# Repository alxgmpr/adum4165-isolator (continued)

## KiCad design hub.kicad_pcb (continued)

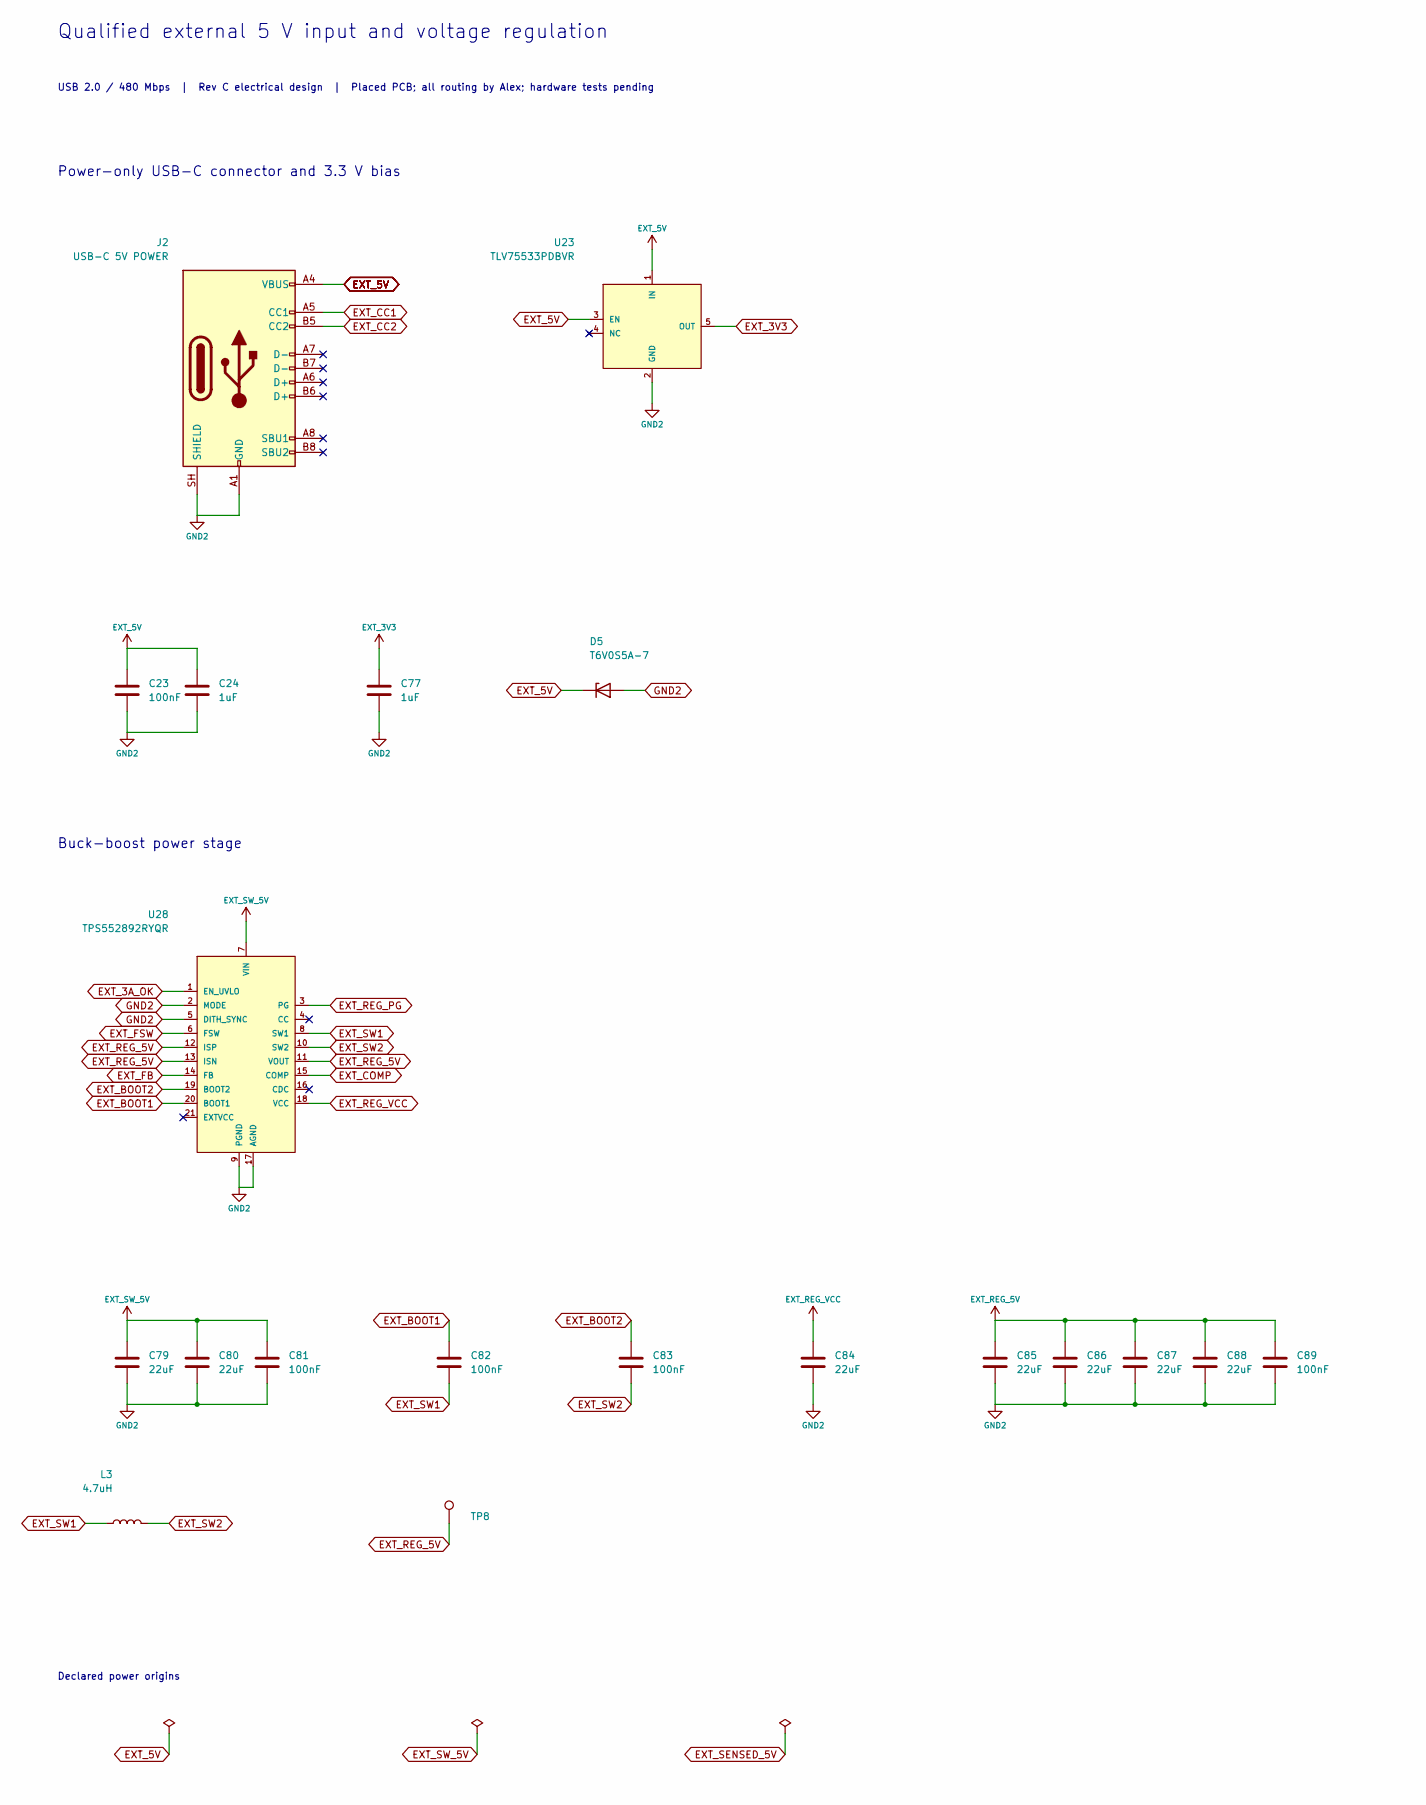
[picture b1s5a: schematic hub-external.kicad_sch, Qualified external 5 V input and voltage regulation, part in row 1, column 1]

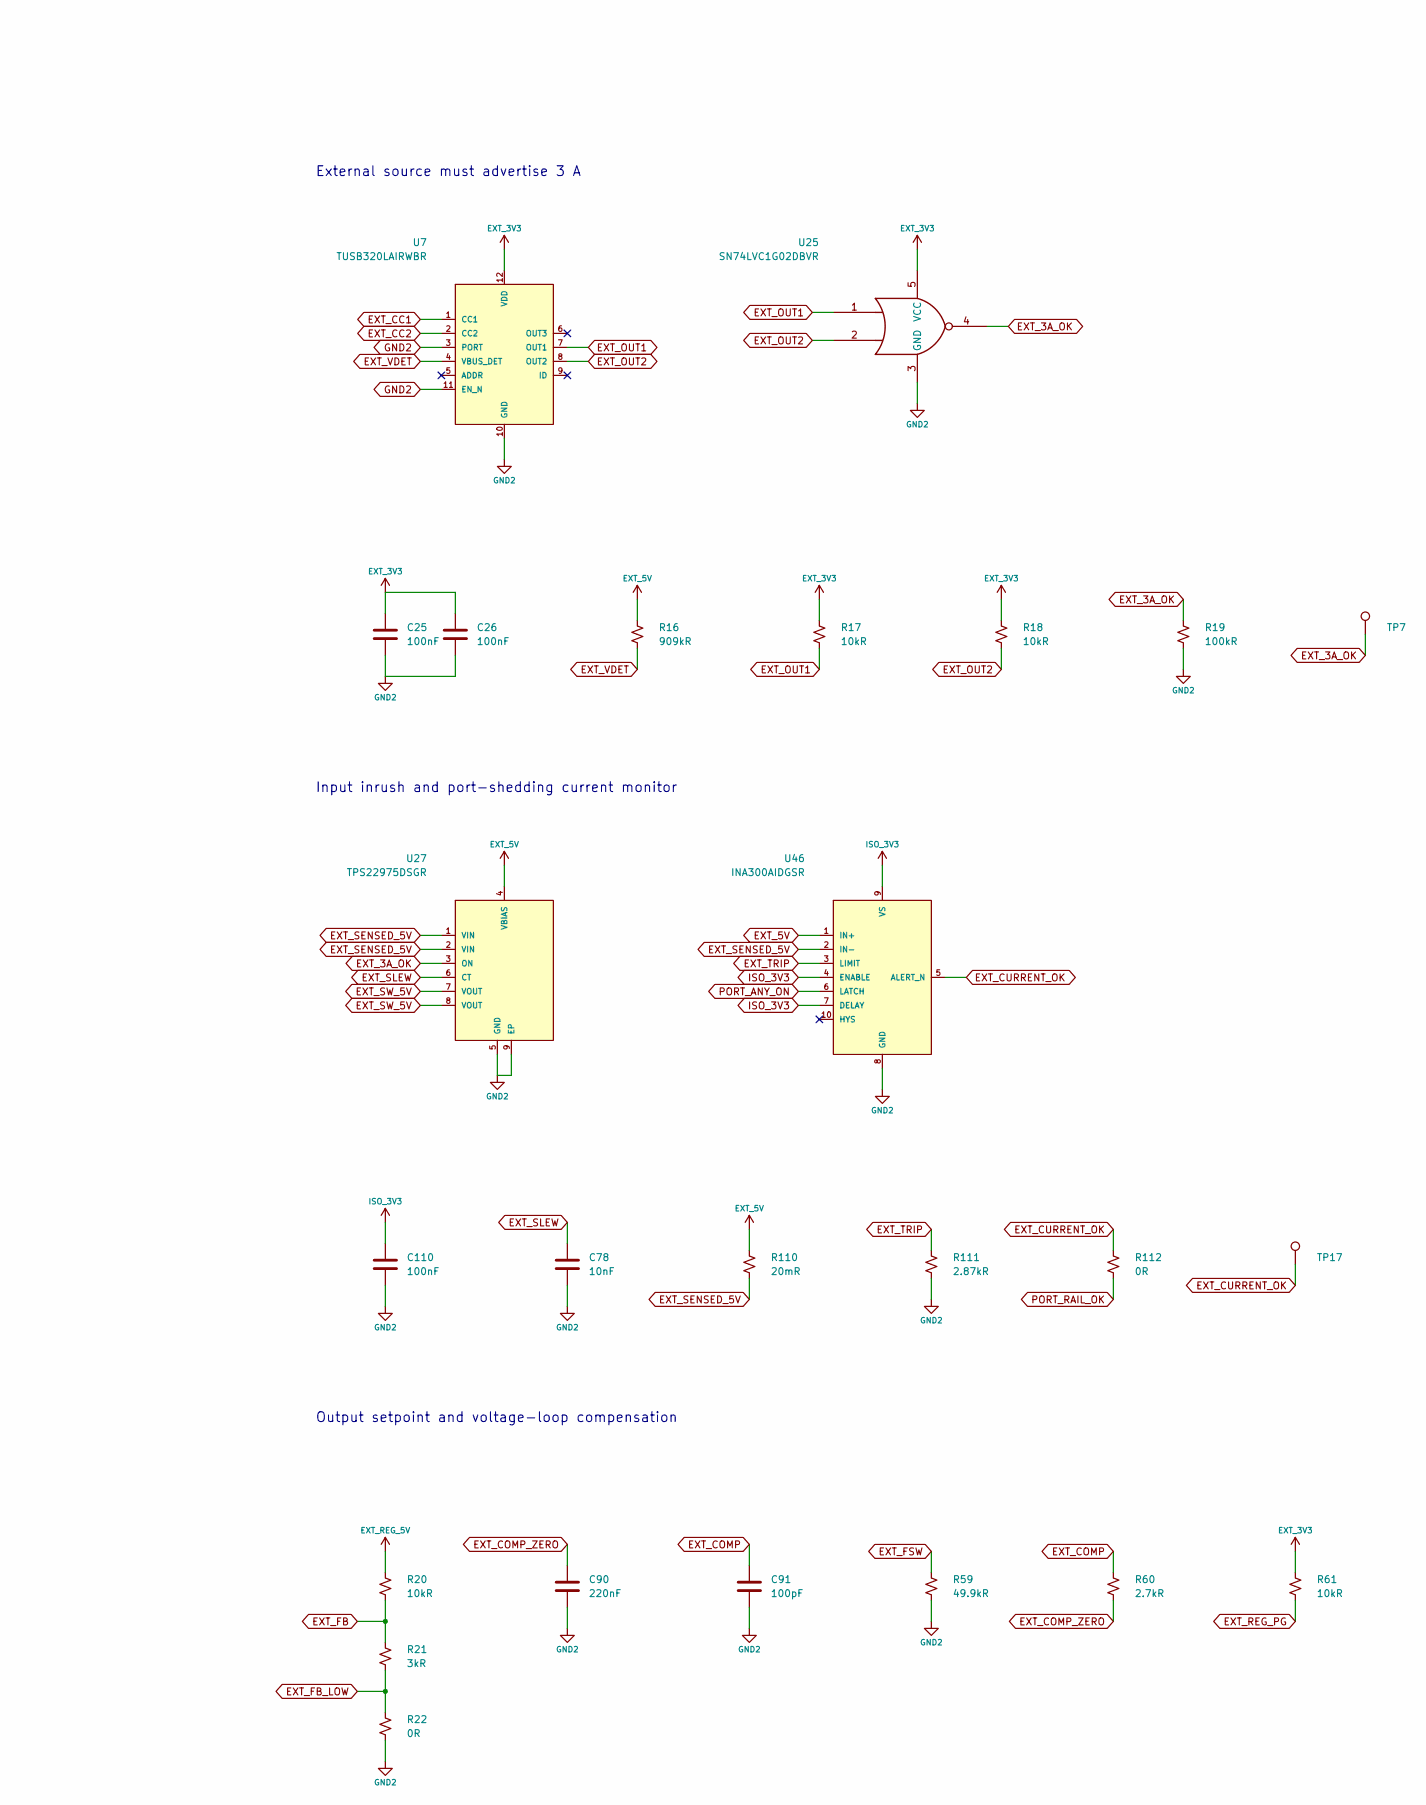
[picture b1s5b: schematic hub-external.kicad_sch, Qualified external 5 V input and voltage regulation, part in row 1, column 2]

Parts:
C23, C25, C26, C81, C82, C83, C89, C110: 100nF; C_0402_1005Metric; Ratings 50V X7R 10%; MPN GRM155R71H104KE14D; LCSC C77020
C24, C77: 1uF; C_0603_1608Metric; Ratings 25V X5R 10%; MPN GRM188R61E105KA12D; LCSC C77046
C78: 10nF; C_0402_1005Metric; Ratings 50V X7R 10%; MPN GRM155R71H103KA88D; LCSC C77019
C79, C80, C84, C85, C86, C87, C88: 22uF; C_1210_3225Metric; Ratings 25V X7R 10%; MPN GRM32ER71E226KE15L; LCSC C21397
C90: 220nF; C_0402_1005Metric; Ratings 16V X7R 10%; MPN GRM155R71C224KA12D; LCSC C77011
C91: 100pF; C_0402_1005Metric; Ratings 50V C0G 5%; MPN GRM1555C1H101JA01D; LCSC C77177
D5: T6V0S5A-7; D_SOD-523; Ratings See exact manufacturer datasheet; MPN T6V0S5A-7; LCSC C19950551
J2: USB-C 5V POWER; USB_C_Receptacle_HRO_TYPE-C-31-M-12; Ratings See exact manufacturer datasheet; MPN TYPE-C-31-M-12; LCSC C165948
L3: 4.7uH; L_Coilcraft_XAL7070-XXX; Ratings See exact manufacturer datasheet; MPN XAL7070-472MEC; LCSC C3911513
R16: 909kR; R_0402_1005Metric; Ratings 1%, 0.1W, 50V; MPN ERJ2RKF9093X; LCSC C2085054
R17, R18, R61: 10kR; R_0402_1005Metric; Ratings 1%, 0.1W, 50V; MPN ERJ2RKF1002X; LCSC C191123
R19: 100kR; R_0402_1005Metric; Ratings 1%, 0.1W, 50V; MPN ERJ2RKF1003X; LCSC C192169
R20: 10kR; R_0603_1608Metric; Ratings 0.1%, 10ppm/C thin film, 0.1W; MPN RT0603BRB0710KL; LCSC C860067
R21: 3kR; R_0603_1608Metric; Ratings 0.1%, 10ppm/C thin film, 0.1W; MPN RT0603BRB073KL; LCSC C860379
R22, R112: 0R; R_0402_1005Metric; Ratings 0R jumper, 0402, 1A rated current; MPN ERJ2GE0R00X; LCSC C242160
R59: 49.9kR; R_0402_1005Metric; Ratings 1%, 0.1W, 50V; MPN ERJ2RKF4992X; LCSC C409918
R60: 2.7kR; R_0402_1005Metric; Ratings 1%, 0.1W, 50V; MPN ERJ2RKF2701X; LCSC C413089
R110: 20mR; R_1206_3216Metric; Ratings 1W, 1%, 75ppm/C; Kelvin sense; MPN WSLP1206R0200FEA; LCSC C441558
R111: 2.87kR; R_0603_1608Metric; Ratings 0.1%, 25ppm/C thin film, 0.1W; MPN RT0603BRD072K87L; LCSC C861305
TP7: EXT_3A_OK; TestPoint_Pad_D1.0mm; Ratings Exposed test pad; no purchased part
TP8: EXT_REG_5V; TestPoint_Pad_D1.0mm; Ratings Exposed test pad; no purchased part
TP17: EXT_CURRENT_OK; TestPoint_Pad_D1.0mm; Ratings Exposed test pad; no purchased part
U7: TUSB320LAIRWBR; Texas_X2QFN-12_1.6x1.6mm_P0.4mm; Ratings See exact manufacturer datasheet; MPN TUSB320LAIRWBR; LCSC C132554
U23: TLV75533PDBVR; SOT-23-5; Ratings See exact manufacturer datasheet; MPN TLV75533PDBVR; LCSC C404027
U25: SN74LVC1G02DBVR; SOT-23-5; Ratings See exact manufacturer datasheet; MPN SN74LVC1G02DBVR; LCSC C16360
U27: TPS22975DSGR; Texas_DSG0008A_WSON-8-1EP_2x2mm_P0.5mm_EP0.9x1.6mm; Ratings See exact manufacturer datasheet; MPN TPS22975DSGR; LCSC C524777
U28: TPS552892RYQR; TI_RYQ0021A_VQFN21_3x5mm; Ratings See exact manufacturer datasheet; MPN TPS552892RYQR; LCSC C19272254
U46: INA300AIDGSR; MSOP-10_3x3mm_P0.5mm; Ratings See exact manufacturer datasheet; MPN INA300AIDGSR; LCSC C529558

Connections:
EXT_3A_OK: R19.1, TP7.1, U25.4, U27.3 (ON), U28.1 (EN_UVLO)
EXT_3V3: C25.1, C26.1, C77.1, R17.1, R18.1, R61.1, U7.12 (VDD), U23.5 (OUT), U25.5 (VCC)
EXT_5V: C23.1, C24.1, D5.1 (K), J2.A4 (VBUS), J2.A9 (VBUS), J2.B4 (VBUS), J2.B9 (VBUS), R16.1, R110.1, U23.1 (IN), U23.3 (EN), U27.4 (VBIAS), U46.1 (IN+)
EXT_BOOT1: C82.1, U28.20 (BOOT1)
EXT_BOOT2: C83.1, U28.19 (BOOT2)
EXT_CC1: J2.A5 (CC1), U7.1 (CC1)
EXT_CC2: J2.B5 (CC2), U7.2 (CC2)
EXT_COMP: C91.1, R60.1, U28.15 (COMP)
EXT_COMP_ZERO: C90.1, R60.2
EXT_CURRENT_OK: R112.1, TP17.1, U46.5 (ALERT_N)
EXT_FB: R20.2, R21.1, U28.14 (FB)
EXT_FB_LOW: R21.2, R22.1
EXT_FSW: R59.1, U28.6 (FSW)
EXT_OUT1: R17.2, U7.7 (OUT1), U25.1
EXT_OUT2: R18.2, U7.8 (OUT2), U25.2
EXT_REG_5V: C85.1, C86.1, C87.1, C88.1, C89.1, R20.1, TP8.1, U28.11 (VOUT), U28.12 (ISP), U28.13 (ISN); also elsewhere on the board
EXT_REG_PG: R61.2, U28.3 (PG)
EXT_REG_VCC: C84.1, U28.18 (VCC)
EXT_SENSED_5V: R110.2, U27.1 (VIN), U27.2 (VIN), U46.2 (IN-)
EXT_SLEW: C78.1, U27.6 (CT)
EXT_SW1: C82.2, L3.1, U28.8 (SW1)
EXT_SW2: C83.2, L3.2, U28.10 (SW2)
EXT_SW_5V: C79.1, C80.1, C81.1, U27.7 (VOUT), U27.8 (VOUT), U28.7 (VIN)
EXT_TRIP: R111.1, U46.3 (LIMIT)
EXT_VDET: R16.2, U7.4 (VBUS_DET)
GND2: C23.2, C24.2, C25.2, C26.2, C77.2, C78.2, C79.2, C80.2, C81.2, C84.2, C85.2, C86.2, C87.2, C88.2, C89.2, C90.2, C91.2, C110.2, D5.2 (A), J2.A1 (GND), J2.A12 (GND), J2.B1 (GND), J2.B12 (GND), J2.SH (SHIELD), R19.2, R22.2, R59.2, R111.2, U7.3 (PORT), U7.10 (GND), U7.11 (EN_N), U23.2 (GND), U25.3 (GND), U27.5 (GND), U27.9 (EP), U28.2 (MODE), U28.5 (DITH_SYNC), U28.9 (PGND), U28.17 (AGND), U46.8 (GND); also elsewhere on the board
ISO_3V3: C110.1, U46.4 (ENABLE), U46.7 (DELAY), U46.9 (VS); also elsewhere on the board
PORT_ANY_ON: U46.6 (LATCH); also elsewhere on the board
PORT_RAIL_OK: R112.2; also elsewhere on the board

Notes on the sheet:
Qualified external 5 V input and voltage regulation
USB 2.0 / 480 Mbps | Rev C electrical design | Placed PCB; all routing by Alex; hardware tests pending
Power-only USB-C connector and 3.3 V bias
External source must advertise 3 A
Input inrush and port-shedding current monitor
Buck-boost power stage
Output setpoint and voltage-loop compensation
Declared power origins

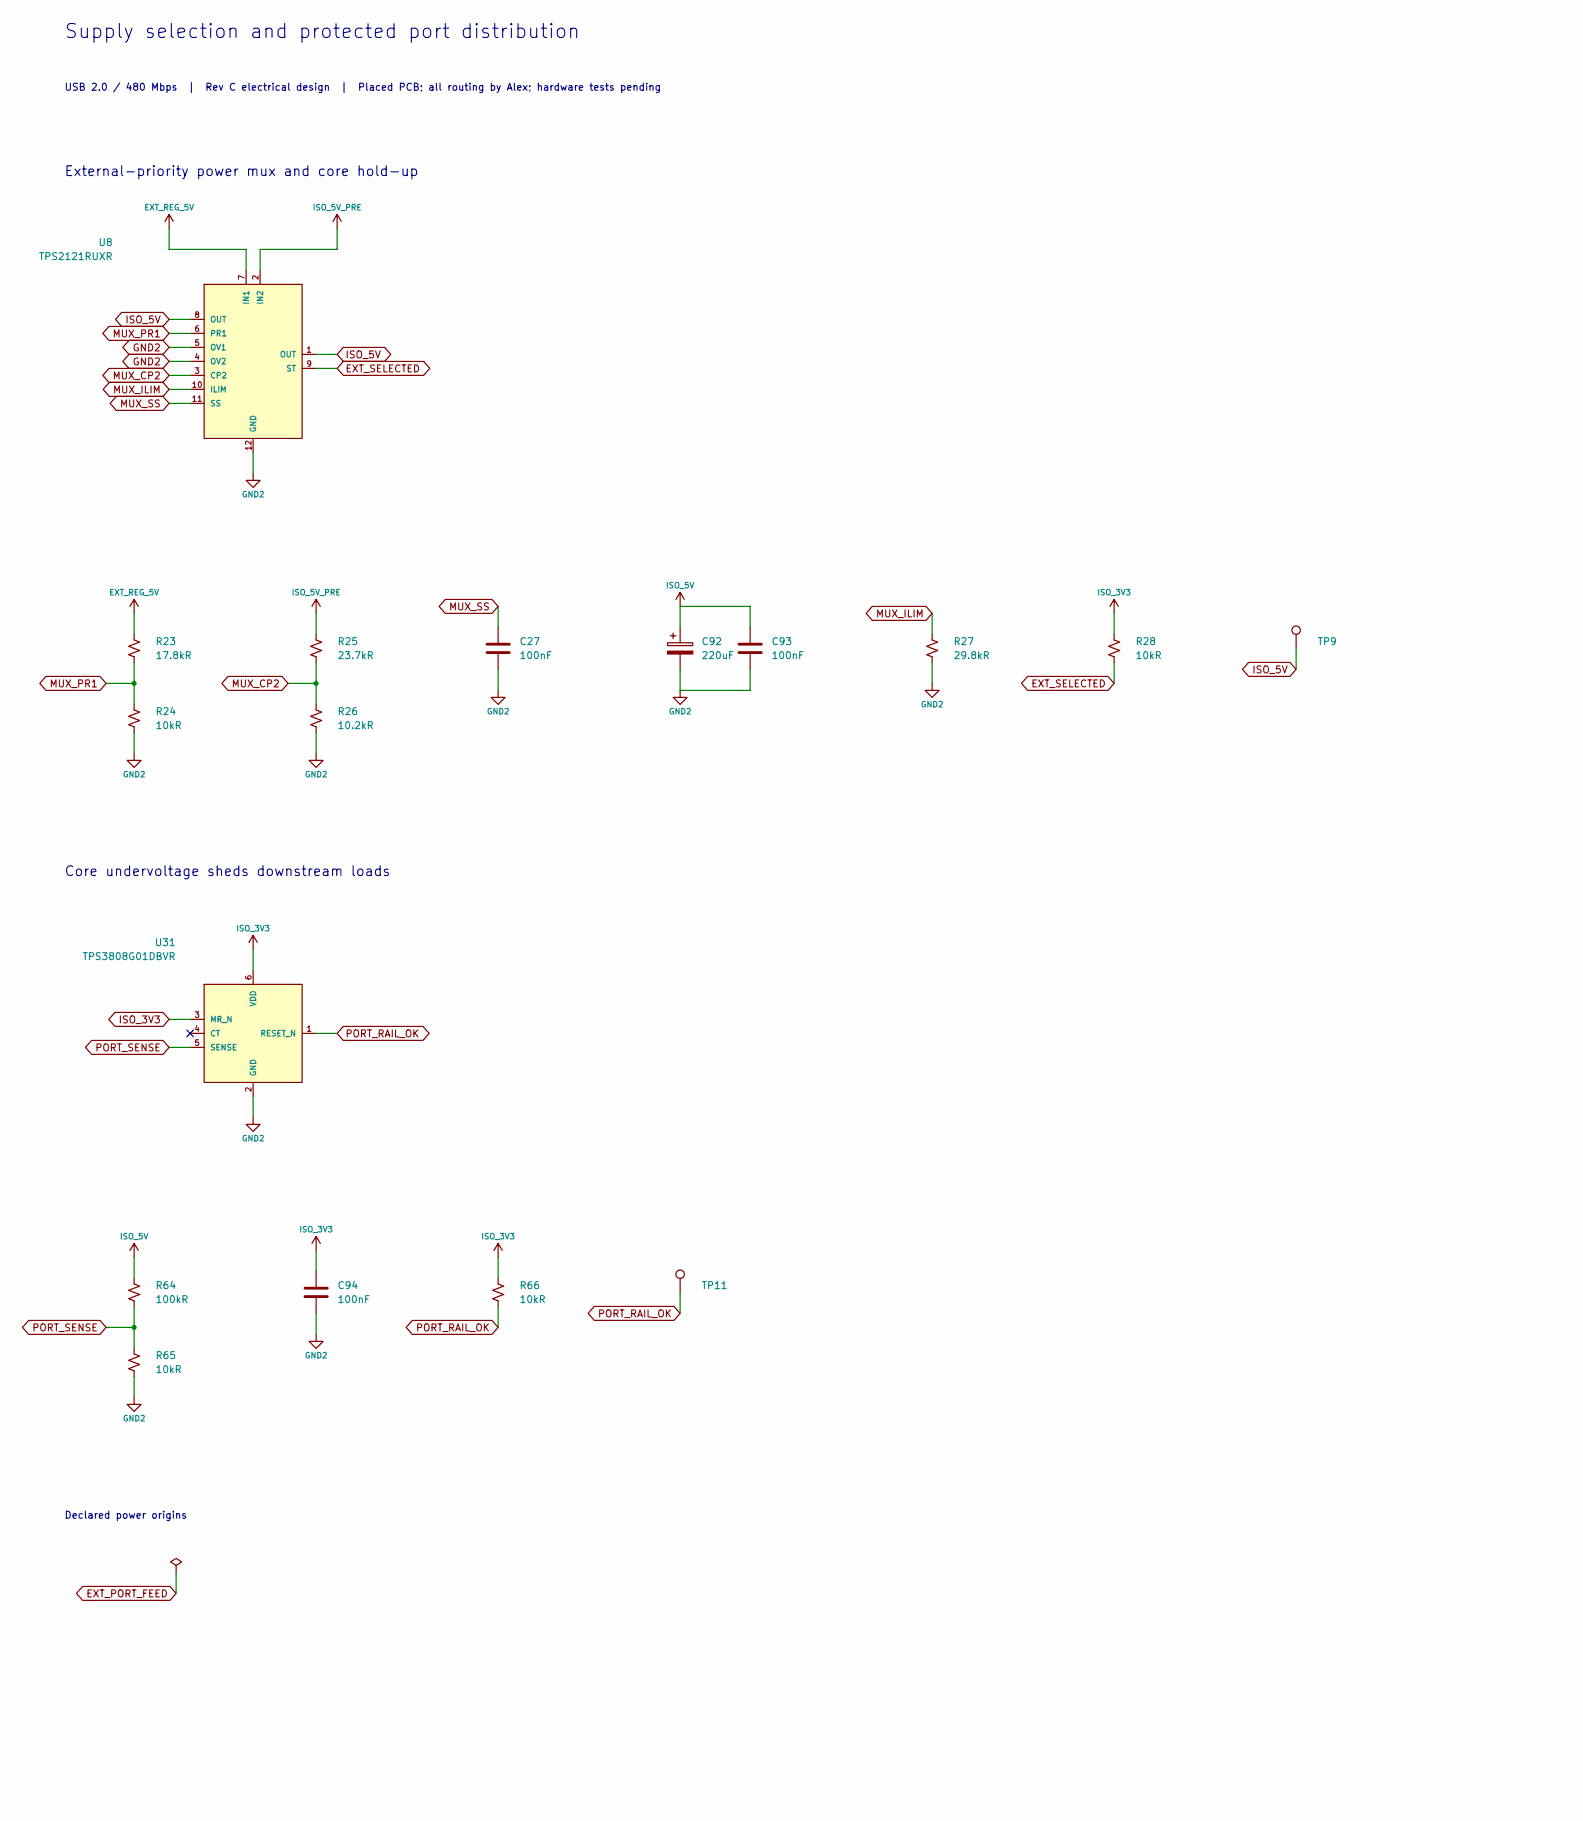
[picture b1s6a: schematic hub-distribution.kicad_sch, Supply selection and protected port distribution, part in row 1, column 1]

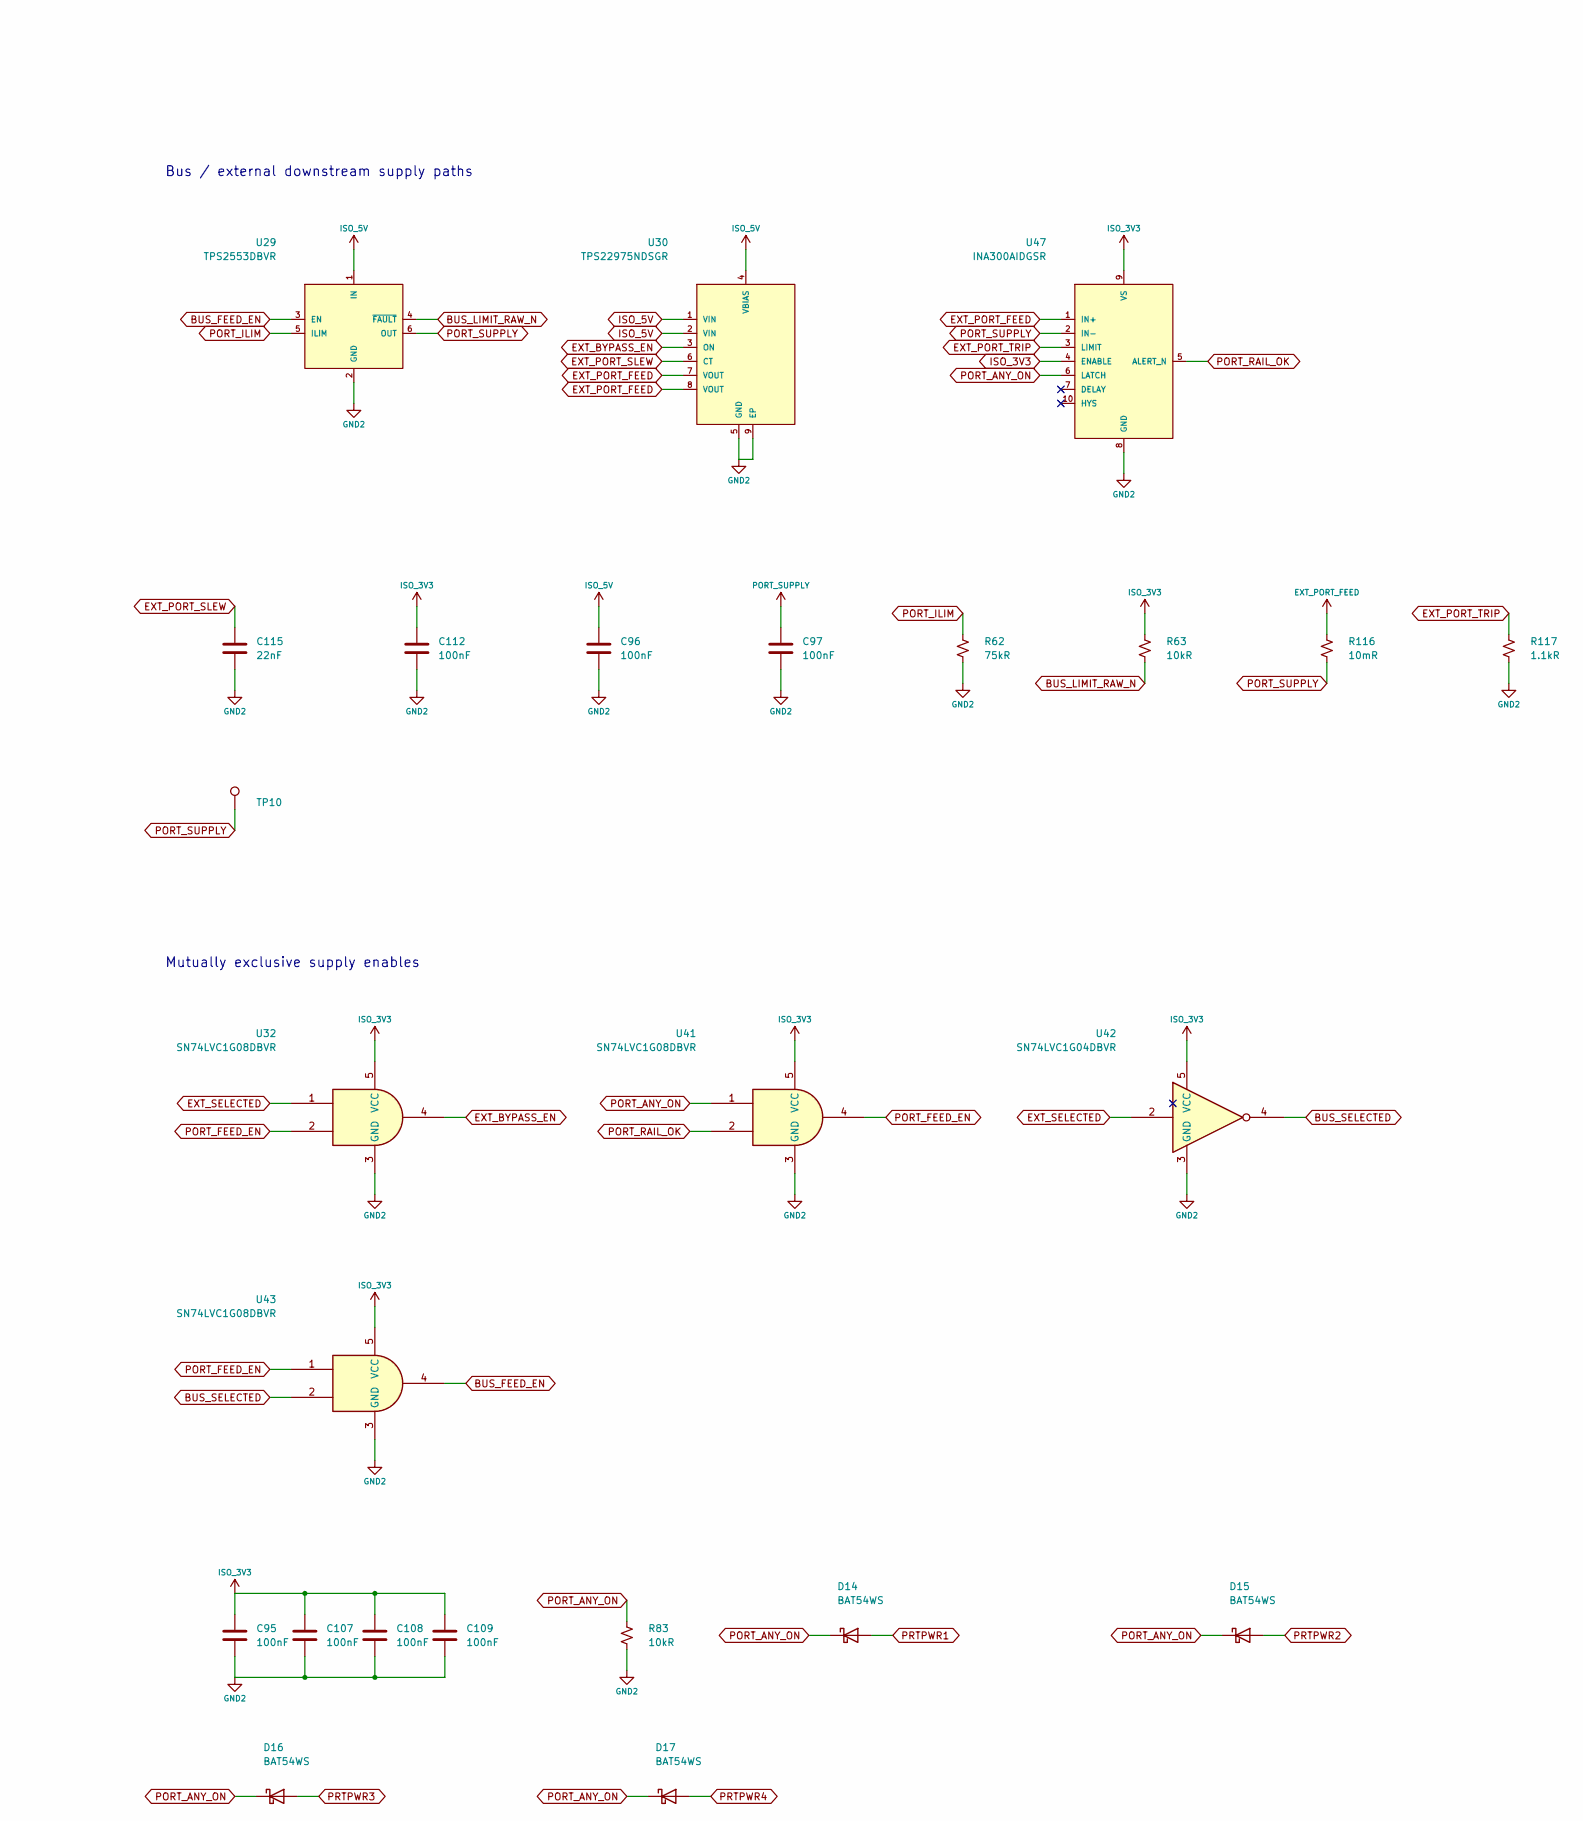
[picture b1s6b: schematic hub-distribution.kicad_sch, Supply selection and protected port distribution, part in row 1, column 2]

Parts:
C27, C93, C94, C95, C96, C97, C107, C108, C109, C112: 100nF; C_0402_1005Metric; Ratings 50V X7R 10%; MPN GRM155R71H104KE14D; LCSC C77020
C92: 220uF; CP_Elec_8x6.2; Ratings 220uF 10V +/-20%; 8mm diameter, 6.5mm m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; MPN EEEFK1A221P; LCSC C401648
C115: 22nF; C_0402_1005Metric; Ratings 50V X7R 10%; MPN GRM155R71H223KA12D; LCSC C77023
D14, D15, D16, D17: BAT54WS; D_SOD-323; Ratings See exact manufacturer datasheet; MPN BAT54WS-7-F; LCSC C124205
R23: 17.8kR; R_0402_1005Metric; Ratings 1%, 0.1W, 50V; MPN ERJ2RKF1782X
R24, R28, R63, R66, R83: 10kR; R_0402_1005Metric; Ratings 1%, 0.1W, 50V; MPN ERJ2RKF1002X; LCSC C191123
R25: 23.7kR; R_0402_1005Metric; Ratings 1%, 0.1W, 50V; MPN ERJ2RKF2372X
R26: 10.2kR; R_0402_1005Metric; Ratings 1%, 0.1W, 50V; MPN ERJ2RKF1022X; LCSC C2076944
R27: 29.8kR; R_0402_1005Metric; Ratings 1%, 0.1W, 50V; MPN ERJ2RKF2982X
R62: 75kR; R_0402_1005Metric; Ratings 1%, 0.1W, 50V; MPN ERJ2RKF7502X; LCSC C413105
R64: 100kR; R_0603_1608Metric; Ratings 0.1%, 10ppm/C thin film, 0.1W; MPN RT0603BRB07100KL; LCSC C860056
R65: 10kR; R_0603_1608Metric; Ratings 0.1%, 10ppm/C thin film, 0.1W; MPN RT0603BRB0710KL; LCSC C860067
R116: 10mR; R_1206_3216Metric; Ratings 1W, 1%, 75ppm/C; Kelvin sense; MPN WSLP1206R0100FEA; LCSC C844910
R117: 1.1kR; R_0603_1608Metric; Ratings 0.1%, 10ppm/C thin film, 0.1W; MPN RT0603BRB071K1L; LCSC C860186
TP9: ISO_5V; TestPoint_Pad_D1.0mm; Ratings Exposed test pad; no purchased part
TP10: PORT_SUPPLY; TestPoint_Pad_D1.0mm; Ratings Exposed test pad; no purchased part
TP11: PORT_RAIL_OK; TestPoint_Pad_D1.0mm; Ratings Exposed test pad; no purchased part
U8: TPS2121RUXR; TI_RUX0012A_VQFN-HR12_2x2.5mm; Ratings See exact manufacturer datasheet; MPN TPS2121RUXR; LCSC C485916
U29: TPS2553DBVR; SOT-23-6; Ratings See exact manufacturer datasheet; MPN TPS2553DBVR; LCSC C55266
U30: TPS22975NDSGR; Texas_DSG0008A_WSON-8-1EP_2x2mm_P0.5mm_EP0.9x1.6mm; Ratings See exact manufacturer datasheet; MPN TPS22975NDSGR; LCSC C2149871
U31: TPS3808G01DBVR; SOT-23-6; Ratings See exact manufacturer datasheet; MPN TPS3808G01DBVR; LCSC C19653
U32, U41, U43: SN74LVC1G08DBVR; SOT-23-5; Ratings See exact manufacturer datasheet; MPN SN74LVC1G08DBVR; LCSC C7666
U42: SN74LVC1G04DBVR; SOT-23-5; Ratings See exact manufacturer datasheet; MPN SN74LVC1G04DBVR; LCSC C7827
U47: INA300AIDGSR; MSOP-10_3x3mm_P0.5mm; Ratings See exact manufacturer datasheet; MPN INA300AIDGSR; LCSC C529558

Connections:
BUS_FEED_EN: U29.3 (EN), U43.4
BUS_LIMIT_RAW_N: R63.2, U29.4 (~FAULT); also elsewhere on the board
BUS_SELECTED: U42.4, U43.2
EXT_BYPASS_EN: U30.3 (ON), U32.4
EXT_PORT_FEED: R116.1, U30.7 (VOUT), U30.8 (VOUT), U47.1 (IN+)
EXT_PORT_SLEW: C115.1, U30.6 (CT)
EXT_PORT_TRIP: R117.1, U47.3 (LIMIT)
EXT_REG_5V: R23.1, U8.7 (IN1); also elsewhere on the board
EXT_SELECTED: R28.2, U8.9 (ST), U32.1, U42.2; also elsewhere on the board
GND2: C27.2, C92.2, C93.2, C94.2, C95.2, C96.2, C97.2, C107.2, C108.2, C109.2, C112.2, C115.2, R24.2, R26.2, R27.2, R62.2, R65.2, R83.2, R117.2, U8.4 (OV2), U8.5 (OV1), U8.12 (GND), U29.2 (GND), U30.5 (GND), U30.9 (EP), U31.2 (GND), U32.3 (GND), U41.3 (GND), U42.3 (GND), U43.3 (GND), U47.8 (GND); also elsewhere on the board
ISO_3V3: C94.1, C95.1, C107.1, C108.1, C109.1, C112.1, R28.1, R63.1, R66.1, U31.3 (MR_N), U31.6 (VDD), U32.5 (VCC), U41.5 (VCC), U42.5 (VCC), U43.5 (VCC), U47.4 (ENABLE), U47.9 (VS); also elsewhere on the board
ISO_5V: C92.1, C93.1, C96.1, R64.1, TP9.1, U8.1 (OUT), U8.8 (OUT), U29.1 (IN), U30.1 (VIN), U30.2 (VIN), U30.4 (VBIAS); also elsewhere on the board
ISO_5V_PRE: R25.1, U8.2 (IN2); also elsewhere on the board
MUX_CP2: R25.2, R26.1, U8.3 (CP2)
MUX_ILIM: R27.1, U8.10 (ILIM)
MUX_PR1: R23.2, R24.1, U8.6 (PR1)
MUX_SS: C27.1, U8.11 (SS)
PORT_ANY_ON: D14.1 (K), D15.1 (K), D16.1 (K), D17.1 (K), R83.1, U41.1, U47.6 (LATCH); also elsewhere on the board
PORT_FEED_EN: U32.2, U41.4, U43.1
PORT_ILIM: R62.1, U29.5 (ILIM)
PORT_RAIL_OK: R66.2, TP11.1, U31.1 (RESET_N), U41.2, U47.5 (ALERT_N); also elsewhere on the board
PORT_SENSE: R64.2, R65.1, U31.5 (SENSE)
PORT_SUPPLY: C97.1, R116.2, TP10.1, U29.6 (OUT), U47.2 (IN-); also elsewhere on the board
PRTPWR1: D14.2 (A); also elsewhere on the board
PRTPWR2: D15.2 (A); also elsewhere on the board
PRTPWR3: D16.2 (A); also elsewhere on the board
PRTPWR4: D17.2 (A); also elsewhere on the board

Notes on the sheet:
Supply selection and protected port distribution
USB 2.0 / 480 Mbps | Rev C electrical design | Placed PCB; all routing by Alex; hardware tests pending
External-priority power mux and core hold-up
Bus / external downstream supply paths
Core undervoltage sheds downstream loads
Mutually exclusive supply enables
Declared power origins

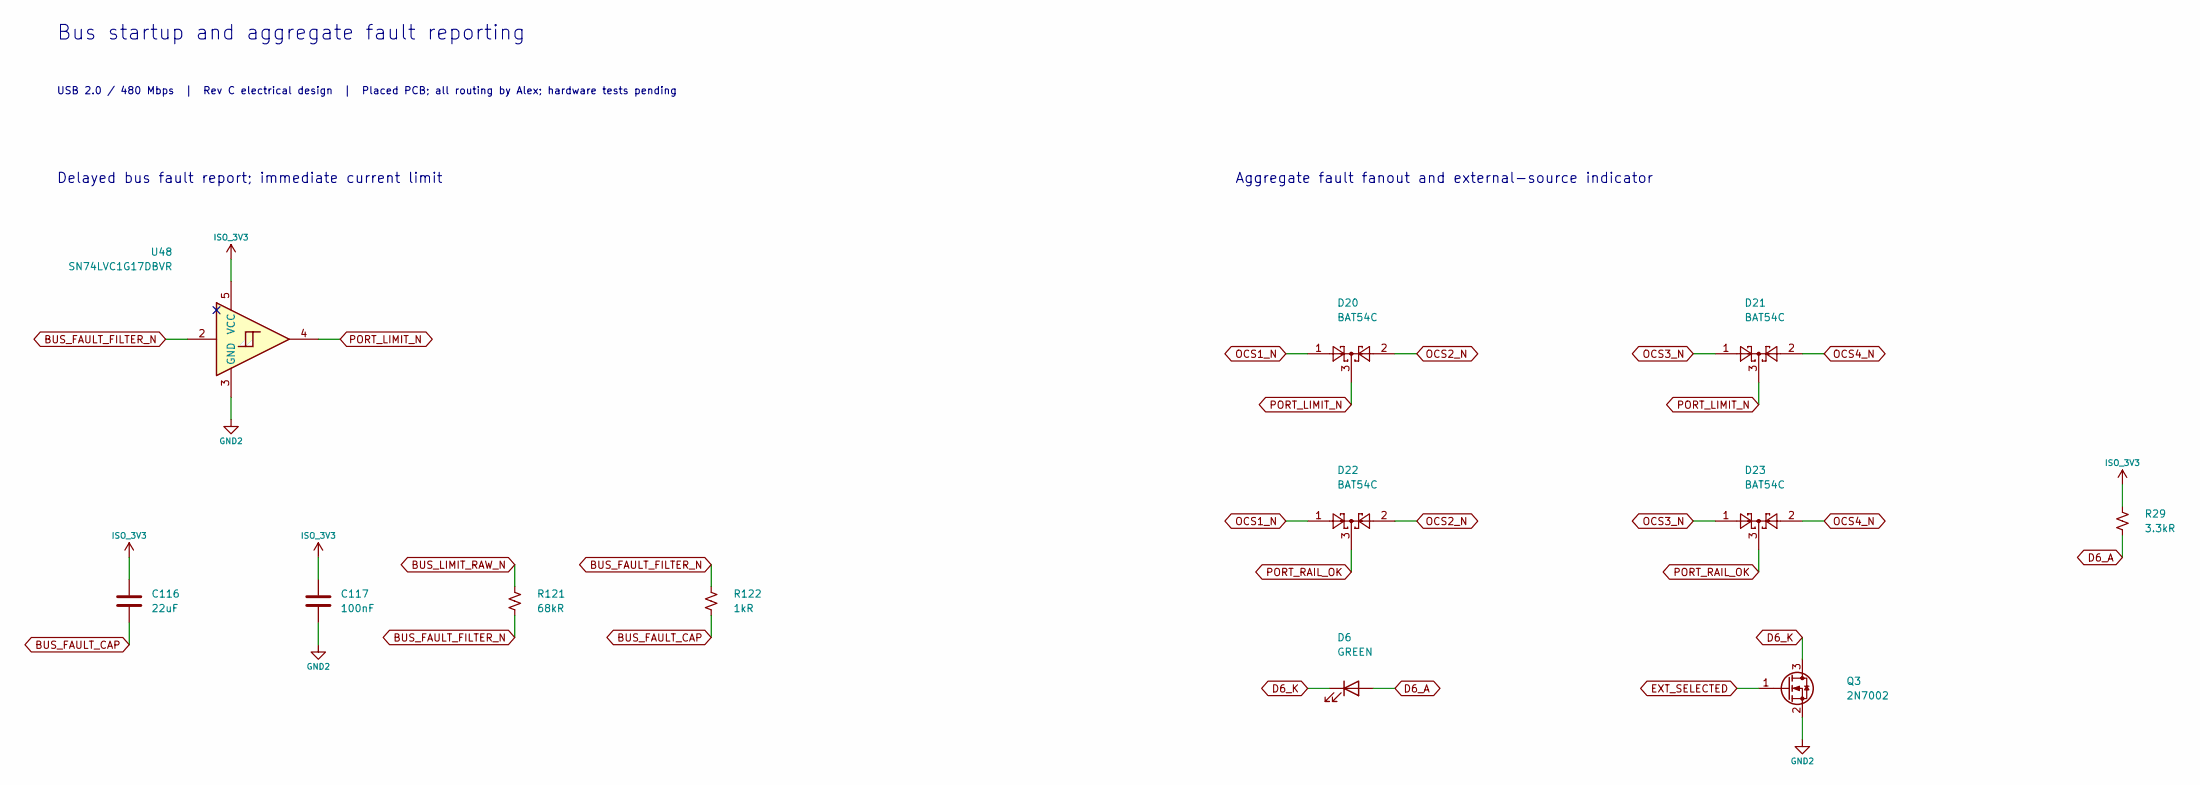
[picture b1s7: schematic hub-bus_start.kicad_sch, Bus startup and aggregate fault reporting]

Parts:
C116: 22uF; C_1210_3225Metric; Ratings 25V X7R 10%; MPN GRM32ER71E226KE15L; LCSC C21397
C117: 100nF; C_0402_1005Metric; Ratings 50V X7R 10%; MPN GRM155R71H104KE14D; LCSC C77020
D6: GREEN; LED_0603_1608Metric; Ratings See exact manufacturer datasheet; MPN LTST-C190KGKT; LCSC C125094
D20, D21, D22, D23: BAT54C; SOT-23; Ratings See exact manufacturer datasheet; MPN BAT54C,215; LCSC C37704
Q3: 2N7002; SOT-23; Ratings See exact manufacturer datasheet; MPN 2N7002,215; LCSC C65189
R29: 3.3kR; R_0402_1005Metric; Ratings 1%, 0.1W, 50V; MPN ERJ2RKF3301X; LCSC C409909
R121: 68kR; R_0402_1005Metric; Ratings 1%, 0.1W, 50V; MPN ERJ2RKF6802X; LCSC C77607
R122: 1kR; R_0402_1005Metric; Ratings 1%, 0.1W, 50V; MPN ERJ2RKF1001X; LCSC C242161
U48: SN74LVC1G17DBVR; SOT-23-5; Ratings See exact manufacturer datasheet; MPN SN74LVC1G17DBVR; LCSC C7836

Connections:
BUS_FAULT_CAP: C116.2, R122.2
BUS_FAULT_FILTER_N: R121.2, R122.1, U48.2
BUS_LIMIT_RAW_N: R121.1; also elsewhere on the board
D6_A: D6.2 (A), R29.2
D6_K: D6.1 (K), Q3.3 (D)
EXT_SELECTED: Q3.1 (G); also elsewhere on the board
GND2: C117.2, Q3.2 (S), U48.3 (GND); also elsewhere on the board
ISO_3V3: C116.1, C117.1, R29.1, U48.5 (VCC); also elsewhere on the board
OCS1_N: D20.1, D22.1; also elsewhere on the board
OCS2_N: D20.2, D22.2; also elsewhere on the board
OCS3_N: D21.1, D23.1; also elsewhere on the board
OCS4_N: D21.2, D23.2; also elsewhere on the board
PORT_LIMIT_N: D20.3, D21.3, U48.4
PORT_RAIL_OK: D22.3, D23.3; also elsewhere on the board

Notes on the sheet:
Bus startup and aggregate fault reporting
USB 2.0 / 480 Mbps | Rev C electrical design | Placed PCB; all routing by Alex; hardware tests pending
Delayed bus fault report; immediate current limit
Aggregate fault fanout and external-source indicator
